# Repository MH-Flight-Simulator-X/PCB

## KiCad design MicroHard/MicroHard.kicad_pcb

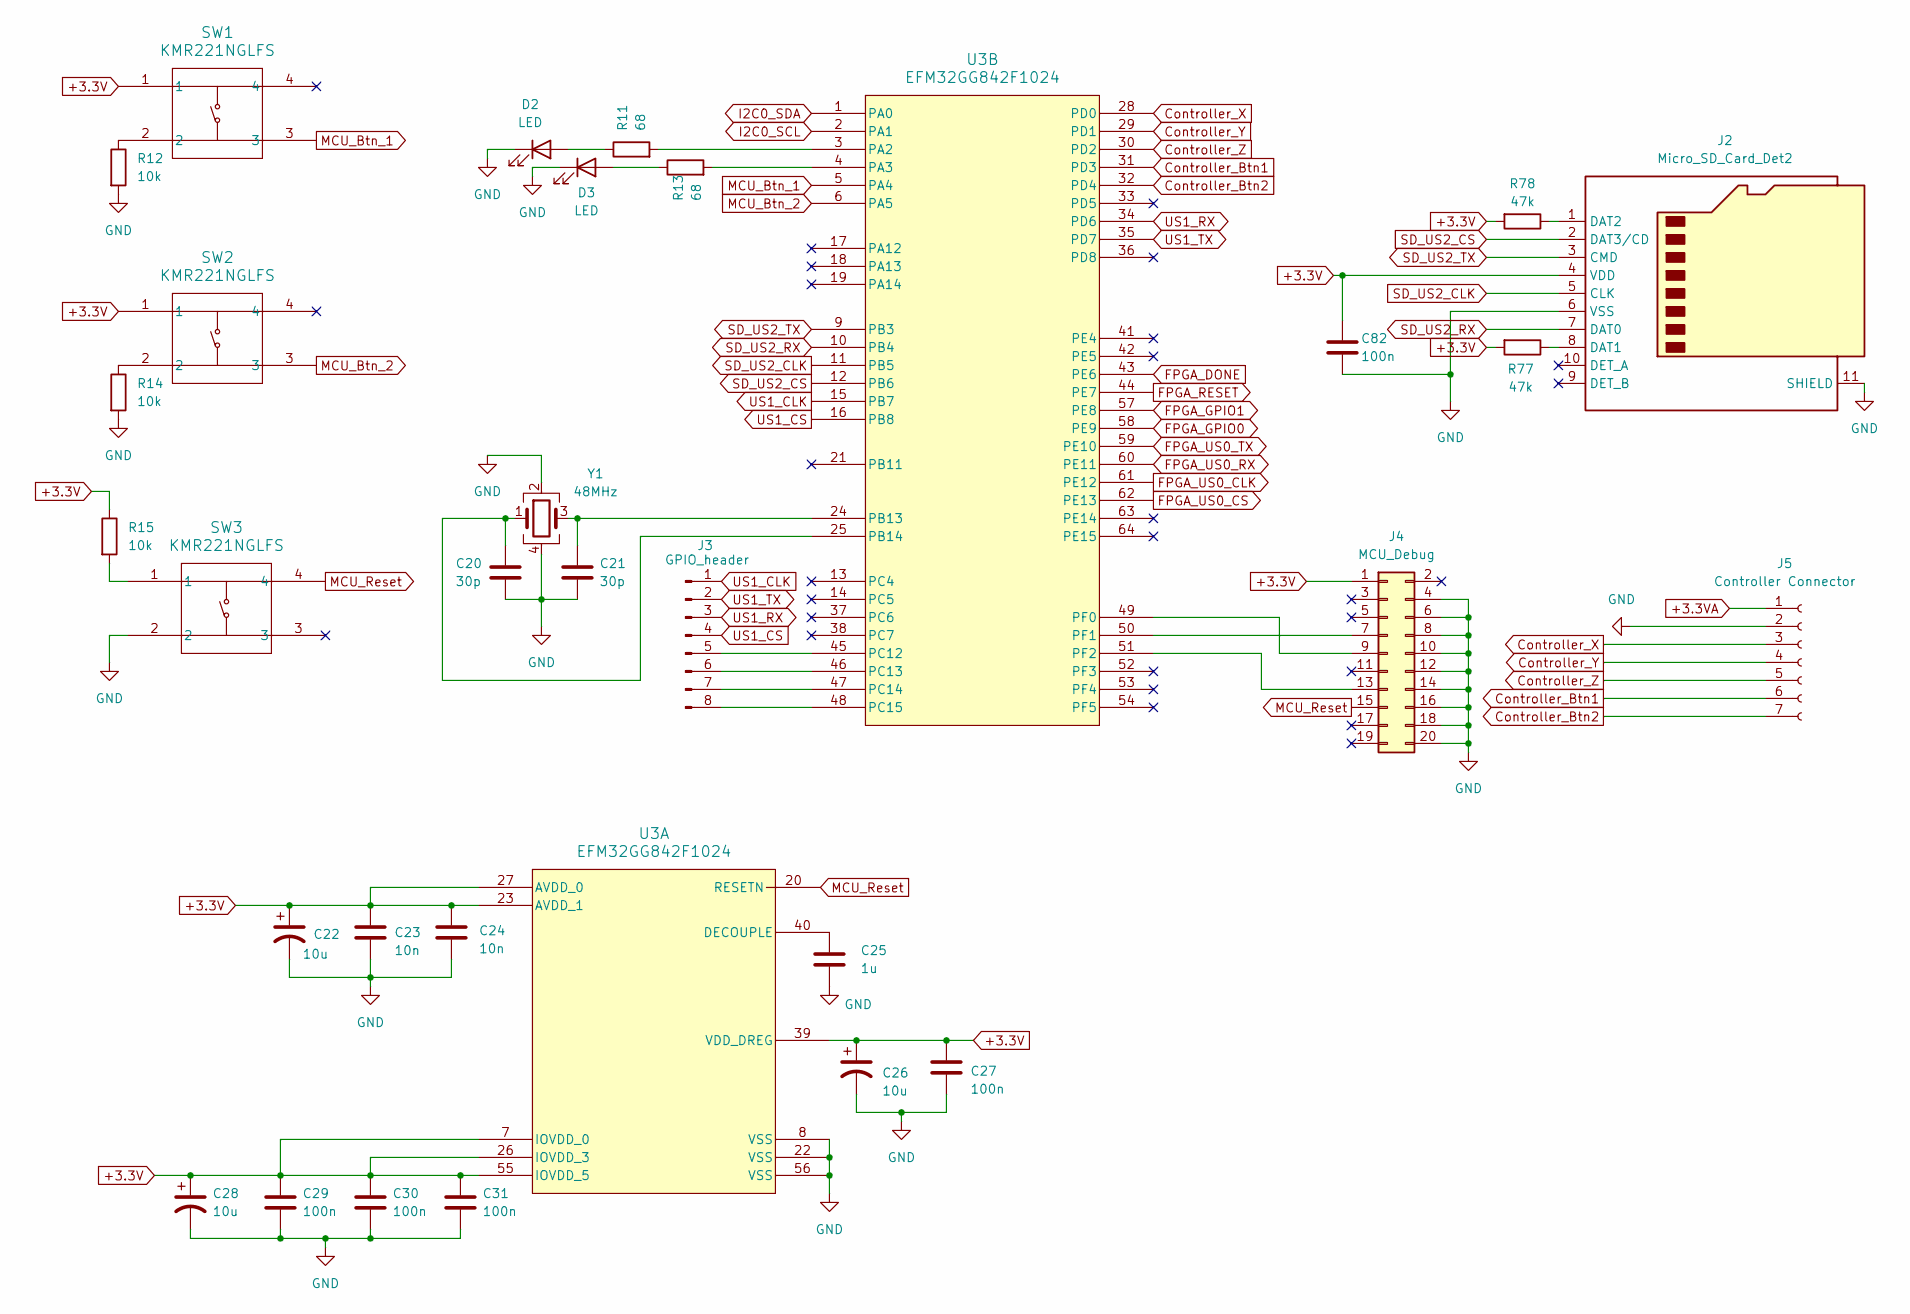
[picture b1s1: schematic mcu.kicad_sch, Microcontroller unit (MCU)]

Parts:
C20, C21: 30p; C_0805_2012Metric_Pad1.18x1.45mm_HandSolder
C22, C26, C28: 10u; C_1206_3216Metric_Pad1.33x1.80mm_HandSolder
C23, C24: 10n; C_1206_3216Metric_Pad1.33x1.80mm_HandSolder
C25: 1u; C_1206_3216Metric_Pad1.33x1.80mm_HandSolder
C27, C29, C30, C31, C82: 100n; C_1206_3216Metric_Pad1.33x1.80mm_HandSolder
D2, D3: LED; LED_1206_3216Metric_Pad1.42x1.75mm_HandSolder
J2: Micro_SD_Card_Det2; microSD_HC_Hirose_DM3AT-SF-PEJM5
J3: GPIO_header; PinHeader_1x08_P2.54mm_Vertical
J4: MCU_Debug; IDC-Header_2x10_P2.54mm_Vertical
J5: Controller Connector; PinHeader_1x07_P2.54mm_Vertical
R11, R13: 68; R_1206_3216Metric_Pad1.30x1.75mm_HandSolder
R12, R14, R15: 10k; R_1206_3216Metric_Pad1.30x1.75mm_HandSolder
R77, R78: 47k; R_1206_3216Metric_Pad1.30x1.75mm_HandSolder
SW1, SW2, SW3: KMR221NGLFS; KMR221_CNK
U3: EFM32GG842F1024; QFP64_10X10
Y1: 48MHz; Crystal_SMD_3225-4Pin_3.2x2.5mm_HandSoldering

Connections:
+3.3V: C22.1, C23.1, C24.1, C26.1, C27.1, C28.1, C29.1, C30.1, C31.1, C82.1, J2.4 (VDD), J4.1, R15.1, R77.2, R78.2, SW1.1, SW2.1, U3.7 (IOVDD_0), U3.23 (AVDD_1), U3.26 (IOVDD_3), U3.27 (AVDD_0), U3.39 (VDD_DREG), U3.55 (IOVDD_5); also elsewhere on the board
+3.3VA: J5.1; also elsewhere on the board
Controller_Btn1: J5.6, U3.31 (PD3)
Controller_Btn2: J5.7, U3.32 (PD4)
Controller_X: J5.3, U3.28 (PD0)
Controller_Y: J5.4, U3.29 (PD1)
Controller_Z: J5.5, U3.30 (PD2)
FPGA_DONE: U3.43 (PE6); also elsewhere on the board
FPGA_GPIO0: U3.58 (PE9); also elsewhere on the board
FPGA_GPIO1: U3.57 (PE8); also elsewhere on the board
FPGA_RESET: U3.44 (PE7); also elsewhere on the board
FPGA_US0_CLK: U3.61 (PE12); also elsewhere on the board
FPGA_US0_CS: U3.62 (PE13); also elsewhere on the board
FPGA_US0_RX: U3.60 (PE11); also elsewhere on the board
FPGA_US0_TX: U3.59 (PE10); also elsewhere on the board
GND: C20.2, C21.2, C22.2, C23.2, C24.2, C25.2, C26.2, C27.2, C28.2, C29.2, C30.2, C31.2, C82.2, D2.1 (K), D3.1 (K), J2.6 (VSS), J2.11 (SHIELD), J4.4, J4.6, J4.8, J4.10, J4.12, J4.14, J4.16, J4.18, J4.20, J5.2, R12.2, R14.2, SW3.2, U3.8 (VSS), U3.22 (VSS), U3.56 (VSS), Y1.2, Y1.4; also elsewhere on the board
I2C0_SCL: U3.2 (PA1); also elsewhere on the board
I2C0_SDA: U3.1 (PA0); also elsewhere on the board
MCU_Btn_1: SW1.3, U3.5 (PA4)
MCU_Btn_2: SW2.3, U3.6 (PA5)
MCU_Reset: J4.15, SW3.4, U3.20 (RESETN)
unnamed: D2.2 (A), R11.1
unnamed: D3.2 (A), R13.1
unnamed: J2.8 (DAT1), R77.1
unnamed: J2.1 (DAT2), R78.1
unnamed: J3.5, U3.45 (PC12)
unnamed: J3.6, U3.46 (PC13)
unnamed: J3.7, U3.47 (PC14)
unnamed: J3.8, U3.48 (PC15)
unnamed: J4.7, U3.50 (PF1)
unnamed: J4.9, U3.49 (PF0)
unnamed: J4.13, U3.51 (PF2)
unnamed: R12.1, SW1.2
unnamed: R14.1, SW2.2
unnamed: R15.2, SW3.1
unnamed: C25.1, U3.40 (DECOUPLE)
unnamed: R11.2, U3.3 (PA2)
unnamed: R13.2, U3.4 (PA3)
unnamed: C21.1, U3.24 (PB13), Y1.3
unnamed: C20.1, U3.25 (PB14), Y1.1
SD_US2_CLK: J2.5 (CLK), U3.11 (PB5)
SD_US2_CS: J2.2 (DAT3/CD), U3.12 (PB6)
SD_US2_RX: J2.7 (DAT0), U3.10 (PB4)
SD_US2_TX: J2.3 (CMD), U3.9 (PB3)
US1_CLK: J3.1, U3.15 (PB7)
US1_CS: J3.4, U3.16 (PB8)
US1_RX: J3.3, U3.34 (PD6)
US1_TX: J3.2, U3.35 (PD7)

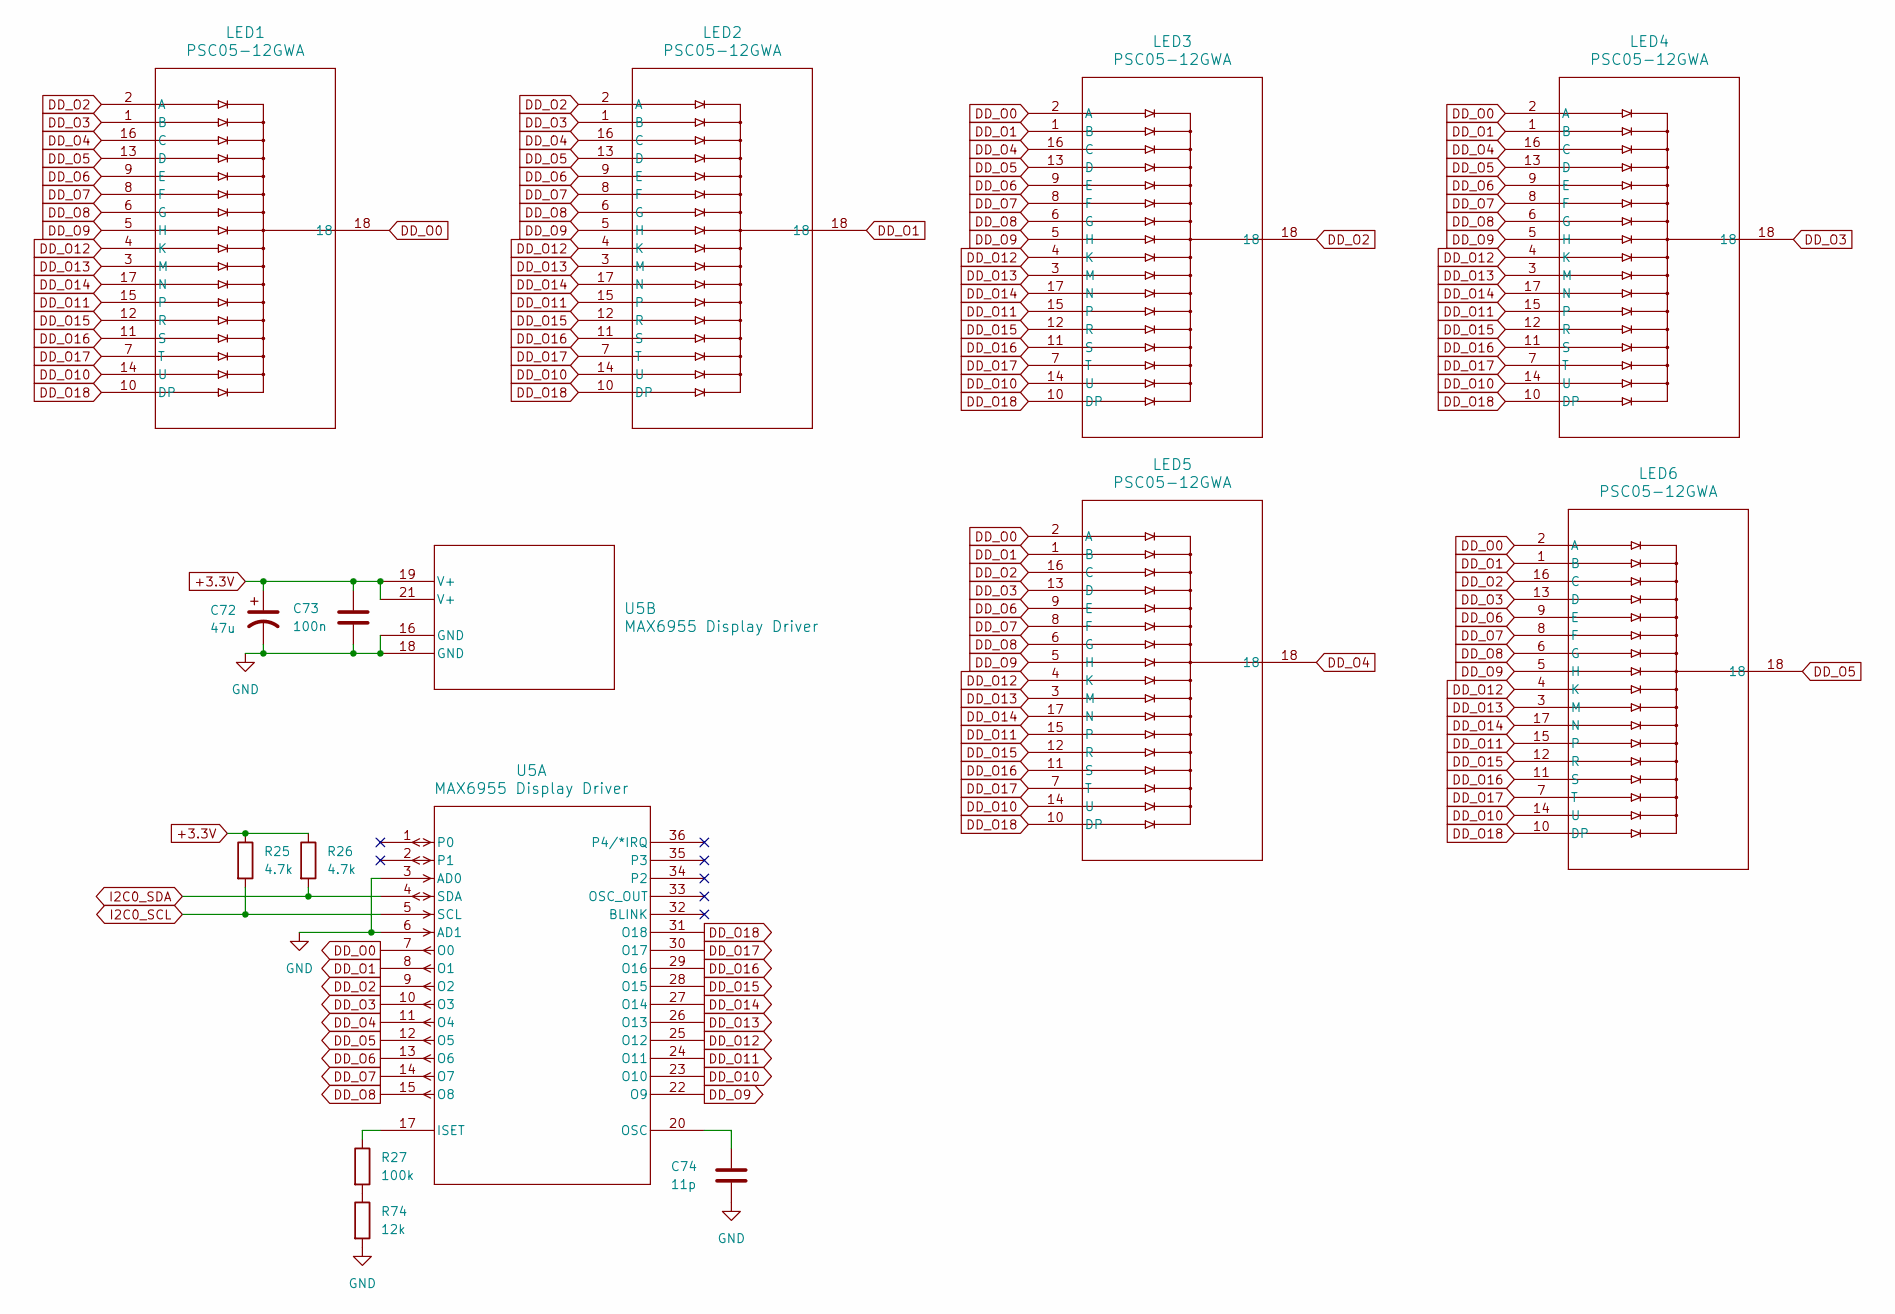
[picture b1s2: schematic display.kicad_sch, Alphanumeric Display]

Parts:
C72: 47u; C_1210_3225Metric_Pad1.33x2.70mm_HandSolder
C73: 100n; C_1206_3216Metric_Pad1.33x1.80mm_HandSolder
C74: 11p; C_0805_2012Metric_Pad1.18x1.45mm_HandSolder
LED1, LED2, LED3, LED4, LED5, LED6: PSC05-12GWA; PSC05-12GWA_LTO
R25, R26: 4.7k; R_1206_3216Metric_Pad1.30x1.75mm_HandSolder
R27: 100k; R_1206_3216Metric_Pad1.30x1.75mm_HandSolder
R74: 12k; R_1206_3216Metric_Pad1.30x1.75mm_HandSolder
U5: MAX6955 Display Driver; 21-0040_A36&plus_2_MXM

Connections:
+3.3V: C72.1, C73.1, R25.1, R26.1, U5.19 (V+), U5.21 (V+); also elsewhere on the board
DD_O0: LED1.18, LED3.2 (A), LED4.2 (A), LED5.2 (A), LED6.2 (A), U5.7 (O0)
DD_O1: LED2.18, LED3.1 (B), LED4.1 (B), LED5.1 (B), LED6.1 (B), U5.8 (O1)
DD_O2: LED1.2 (A), LED2.2 (A), LED3.18, LED5.16 (C), LED6.16 (C), U5.9 (O2)
DD_O3: LED1.1 (B), LED2.1 (B), LED4.18, LED5.13 (D), LED6.13 (D), U5.10 (O3)
DD_O4: LED1.16 (C), LED2.16 (C), LED3.16 (C), LED4.16 (C), LED5.18, U5.11 (O4)
DD_O5: LED1.13 (D), LED2.13 (D), LED3.13 (D), LED4.13 (D), LED6.18, U5.12 (O5)
DD_O6: LED1.9 (E), LED2.9 (E), LED3.9 (E), LED4.9 (E), LED5.9 (E), LED6.9 (E), U5.13 (O6)
DD_O7: LED1.8 (F), LED2.8 (F), LED3.8 (F), LED4.8 (F), LED5.8 (F), LED6.8 (F), U5.14 (O7)
DD_O8: LED1.6 (G), LED2.6 (G), LED3.6 (G), LED4.6 (G), LED5.6 (G), LED6.6 (G), U5.15 (O8)
DD_O9: LED1.5 (H), LED2.5 (H), LED3.5 (H), LED4.5 (H), LED5.5 (H), LED6.5 (H), U5.22 (O9)
DD_O10: LED1.14 (U), LED2.14 (U), LED3.14 (U), LED4.14 (U), LED5.14 (U), LED6.14 (U), U5.23 (O10)
DD_O11: LED1.15, LED2.15, LED3.15, LED4.15, LED5.15, LED6.15, U5.24 (O11)
DD_O12: LED1.4 (K), LED2.4 (K), LED3.4 (K), LED4.4 (K), LED5.4 (K), LED6.4 (K), U5.25 (O12)
DD_O13: LED1.3 (M), LED2.3 (M), LED3.3 (M), LED4.3 (M), LED5.3 (M), LED6.3 (M), U5.26 (O13)
DD_O14: LED1.17 (N), LED2.17 (N), LED3.17 (N), LED4.17 (N), LED5.17 (N), LED6.17 (N), U5.27 (O14)
DD_O15: LED1.12 (R), LED2.12 (R), LED3.12 (R), LED4.12 (R), LED5.12 (R), LED6.12 (R), U5.28 (O15)
DD_O16: LED1.11 (S), LED2.11 (S), LED3.11 (S), LED4.11 (S), LED5.11 (S), LED6.11 (S), U5.29 (O16)
DD_O17: LED1.7 (T), LED2.7 (T), LED3.7 (T), LED4.7 (T), LED5.7 (T), LED6.7 (T), U5.30 (O17)
DD_O18: LED1.10 (DP), LED2.10 (DP), LED3.10 (DP), LED4.10 (DP), LED5.10 (DP), LED6.10 (DP), U5.31 (O18)
GND: C72.2, C73.2, C74.2, R74.2, U5.3 (AD0), U5.6 (AD1), U5.16 (GND), U5.18 (GND); also elsewhere on the board
I2C0_SCL: R25.2, U5.5 (SCL); also elsewhere on the board
I2C0_SDA: R26.2, U5.4 (SDA); also elsewhere on the board
unnamed: R27.2, R74.1
unnamed: R27.1, U5.17 (ISET)
unnamed: C74.1, U5.20 (OSC)

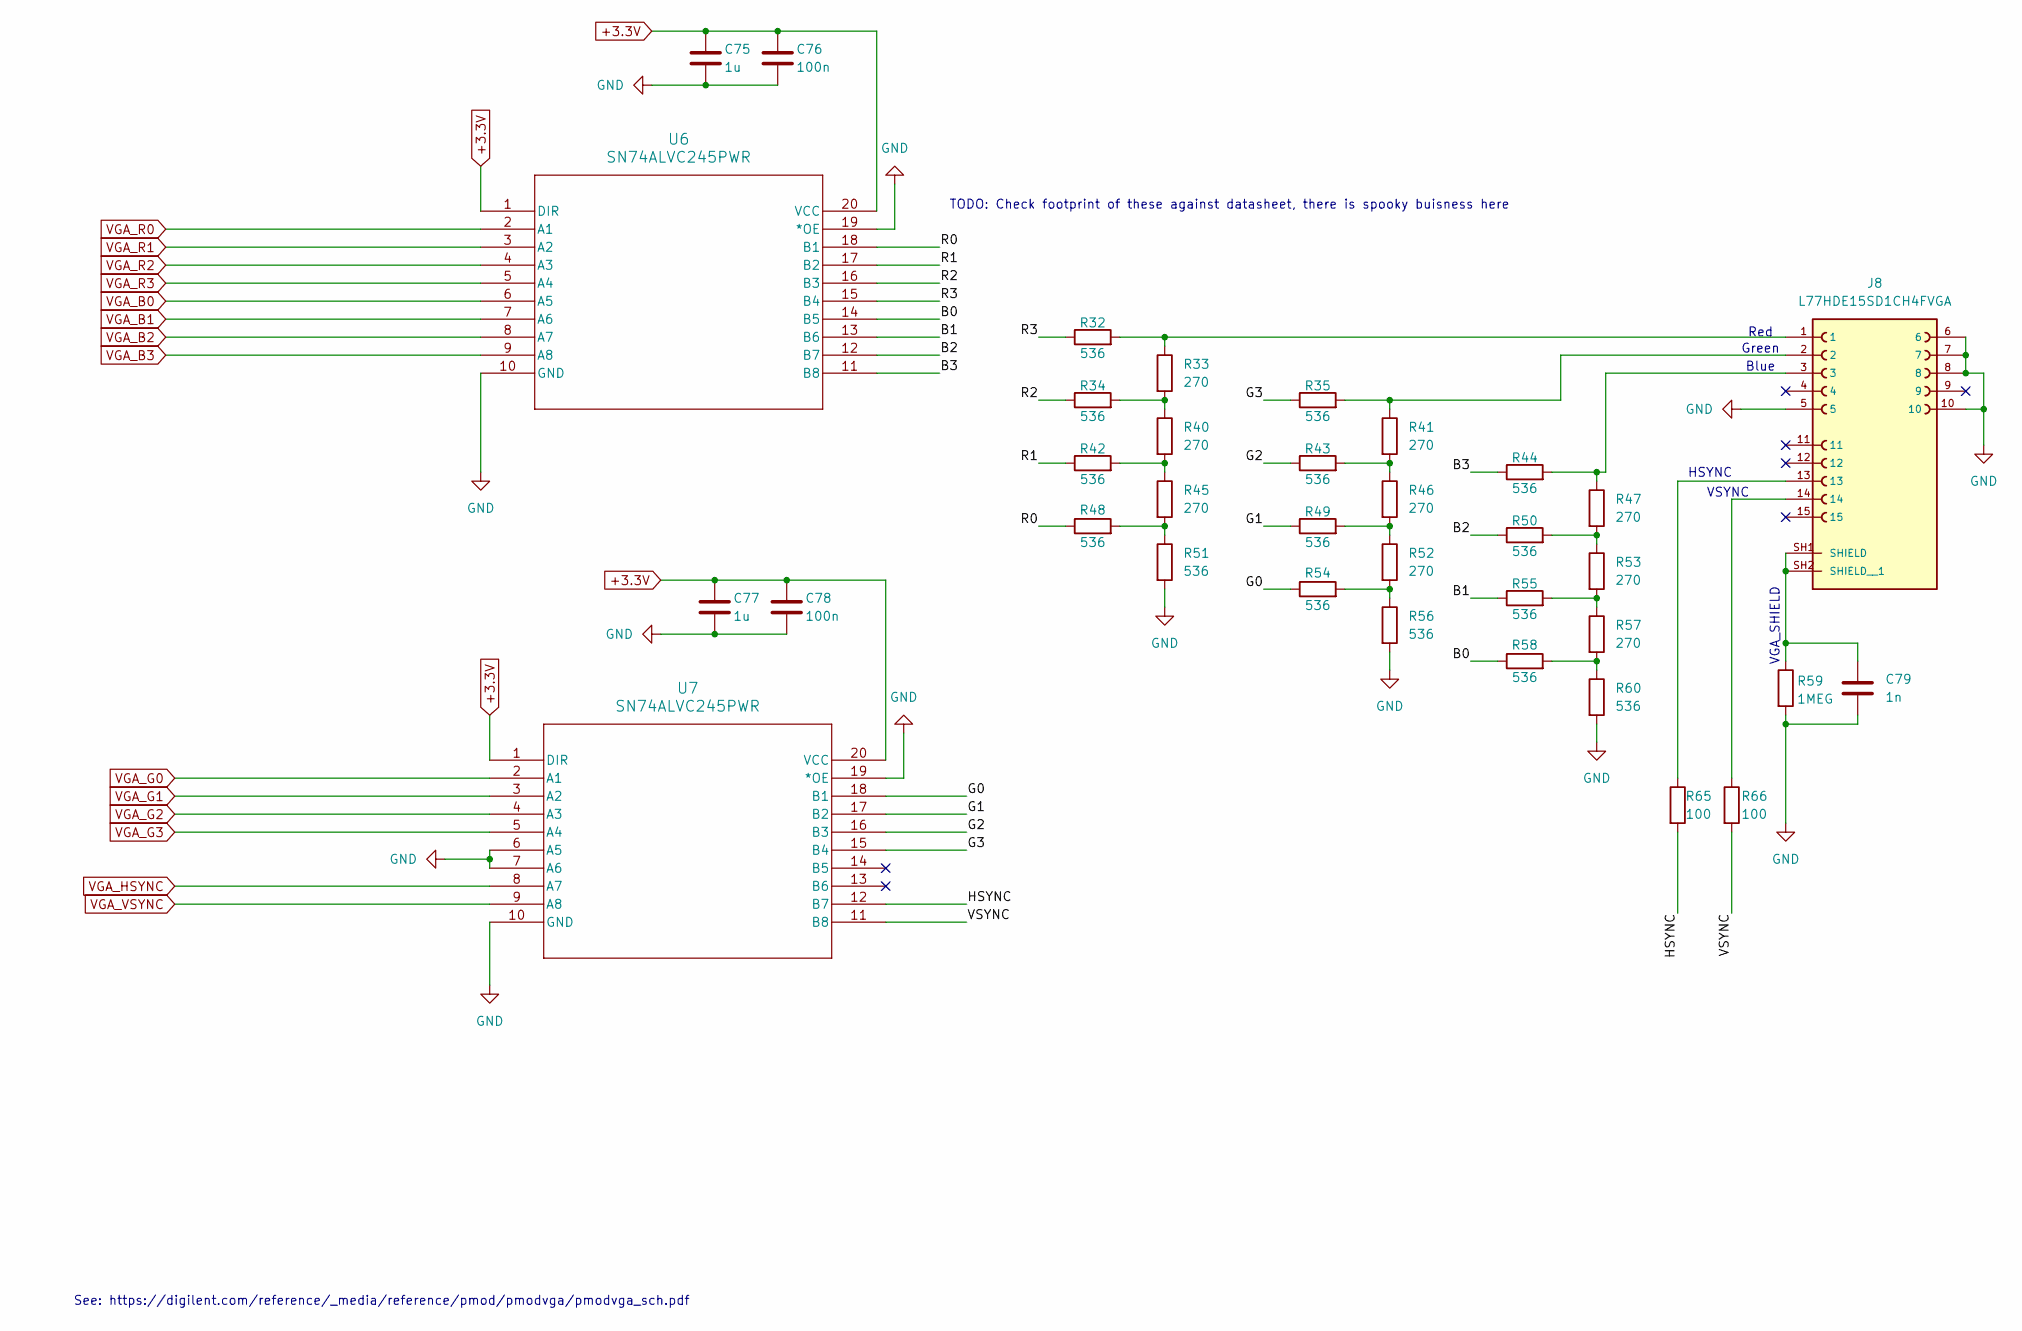
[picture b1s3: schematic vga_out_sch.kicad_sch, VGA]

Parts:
C75, C77: 1u; C_1206_3216Metric_Pad1.33x1.80mm_HandSolder
C76, C78: 100n; C_1206_3216Metric_Pad1.33x1.80mm_HandSolder
C79: 1n; C_0805_2012Metric_Pad1.18x1.45mm_HandSolder
J8: L77HDE15SD1CH4FVGA; AMPHENOL_L77HDE15SD1CH4FVGA; PARTREV 1
R32, R34, R35, R42, R43, R44, R48, R49, R50, R51, R54, R55, R56, R58, R60: 536; R_1206_3216Metric_Pad1.30x1.75mm_HandSolder
R33, R40, R41, R45, R46, R47, R52, R53, R57: 270; R_1206_3216Metric_Pad1.30x1.75mm_HandSolder
R59: 1MEG; R_1206_3216Metric_Pad1.30x1.75mm_HandSolder
R65, R66: 100; R_1206_3216Metric_Pad1.30x1.75mm_HandSolder
U6, U7: SN74ALVC245PWR; PW20

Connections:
+3.3V: C75.1, C76.1, C77.1, C78.1, U6.1 (DIR), U6.20 (VCC), U7.1 (DIR), U7.20 (VCC); also elsewhere on the board
/VGA out/B0: R58.1, U6.14 (B5)
/VGA out/B1: R55.1, U6.13 (B6)
/VGA out/B2: R50.1, U6.12 (B7)
/VGA out/B3: R44.1, U6.11 (B8)
/VGA out/G0: R54.1, U7.18 (B1)
/VGA out/G1: R49.1, U7.17 (B2)
/VGA out/G2: R43.1, U7.16 (B3)
/VGA out/G3: R35.1, U7.15 (B4)
/VGA out/HSYNC: R65.2, U7.12 (B7)
/VGA out/R0: R48.1, U6.18 (B1)
/VGA out/R1: R42.1, U6.17 (B2)
/VGA out/R2: R34.1, U6.16 (B3)
/VGA out/R3: R32.1, U6.15 (B4)
/VGA out/VSYNC: R66.2, U7.11 (B8)
GND: C75.2, C76.2, C77.2, C78.2, C79.2, J8.5, J8.6, J8.7, J8.8, J8.10, R51.2, R56.2, R59.2, R60.2, U6.10 (GND), U6.19 (*OE), U7.6 (A5), U7.7 (A6), U7.10 (GND), U7.19 (*OE); also elsewhere on the board
unnamed: J8.1, R32.2, R33.1
unnamed: J8.2, R35.2, R41.1
unnamed: J8.3, R44.2, R47.1
unnamed: J8.13, R65.1
unnamed: J8.14, R66.1
unnamed: C79.1, J8.SH1 (SHIELD), J8.SH2 (SHIELD__1), R59.1
unnamed: R33.2, R34.2, R40.1
unnamed: R40.2, R42.2, R45.1
unnamed: R41.2, R43.2, R46.1
unnamed: R45.2, R48.2, R51.1
unnamed: R46.2, R49.2, R52.1
unnamed: R47.2, R50.2, R53.1
unnamed: R52.2, R54.2, R56.1
unnamed: R53.2, R55.2, R57.1
unnamed: R57.2, R58.2, R60.1
VGA_B0: U6.6 (A5); also elsewhere on the board
VGA_B1: U6.7 (A6); also elsewhere on the board
VGA_B2: U6.8 (A7); also elsewhere on the board
VGA_B3: U6.9 (A8); also elsewhere on the board
VGA_G0: U7.2 (A1); also elsewhere on the board
VGA_G1: U7.3 (A2); also elsewhere on the board
VGA_G2: U7.4 (A3); also elsewhere on the board
VGA_G3: U7.5 (A4); also elsewhere on the board
VGA_HSYNC: U7.8 (A7); also elsewhere on the board
VGA_R0: U6.2 (A1); also elsewhere on the board
VGA_R1: U6.3 (A2); also elsewhere on the board
VGA_R2: U6.4 (A3); also elsewhere on the board
VGA_R3: U6.5 (A4); also elsewhere on the board
VGA_VSYNC: U7.9 (A8); also elsewhere on the board

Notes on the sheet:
HSYNC
Blue
VGA_SHIELD
Green
See: https://digilent.com/reference/_media/reference/pmod/pmodvga/pmodvga_sch.pdf
TODO: Check footprint of these against datasheet, there is spooky buisness here
Red
VSYNC

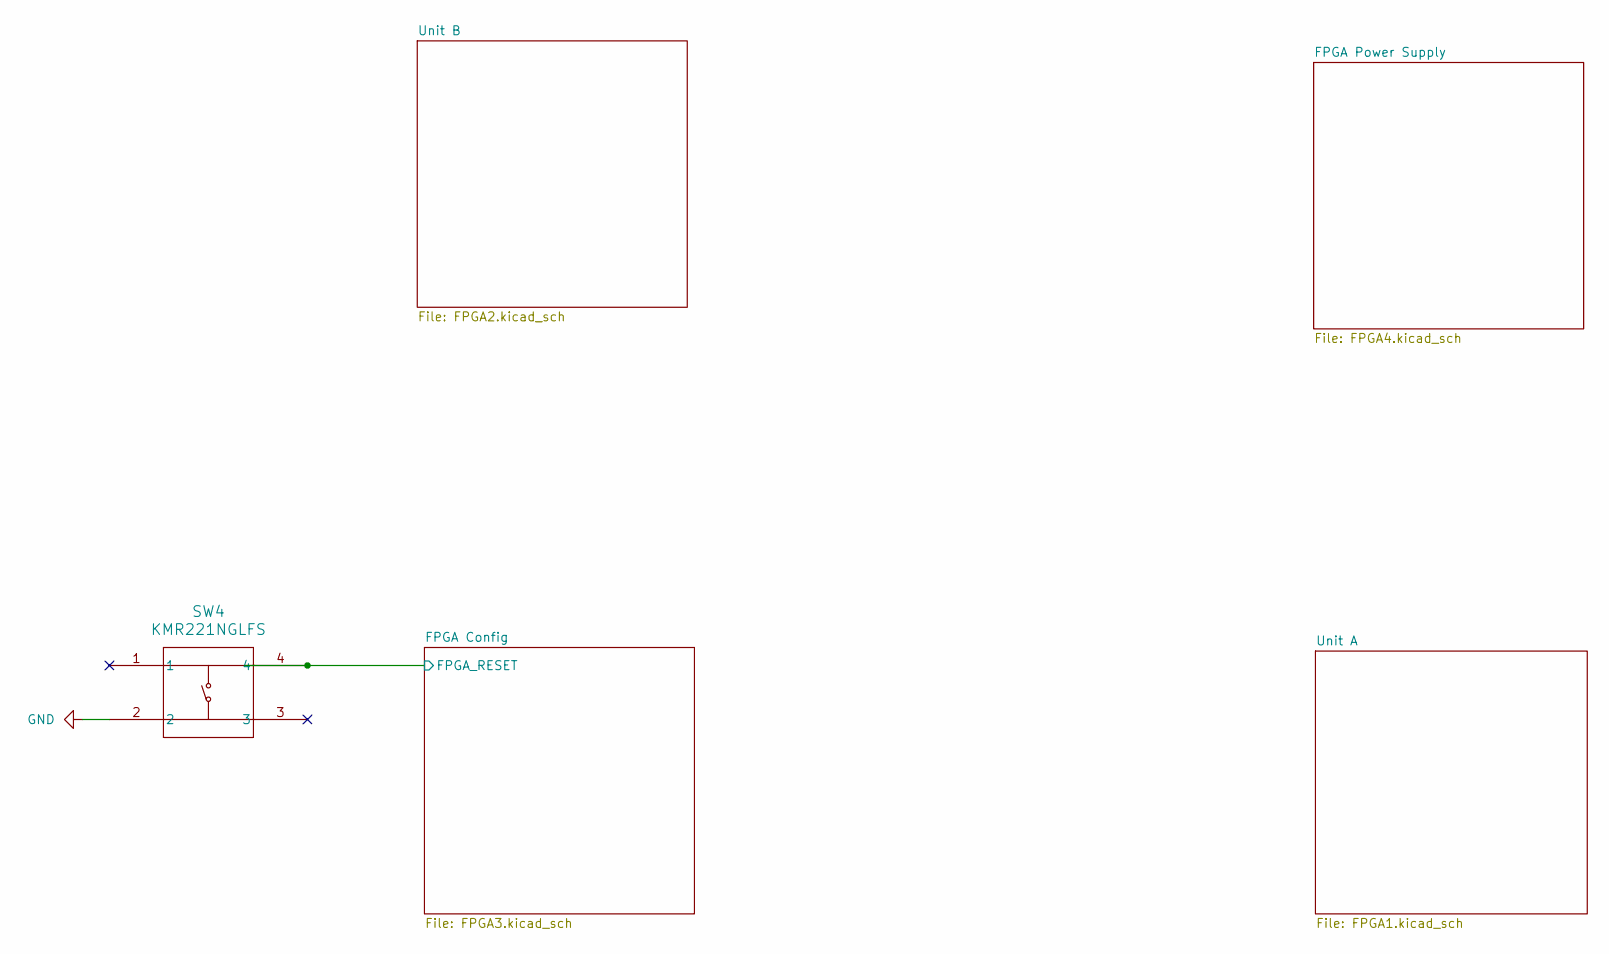
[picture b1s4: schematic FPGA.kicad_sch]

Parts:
SW4: KMR221NGLFS; KMR221_CNK

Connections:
FPGA_RESET: SW4.4; also elsewhere on the board
GND: SW4.2; also elsewhere on the board

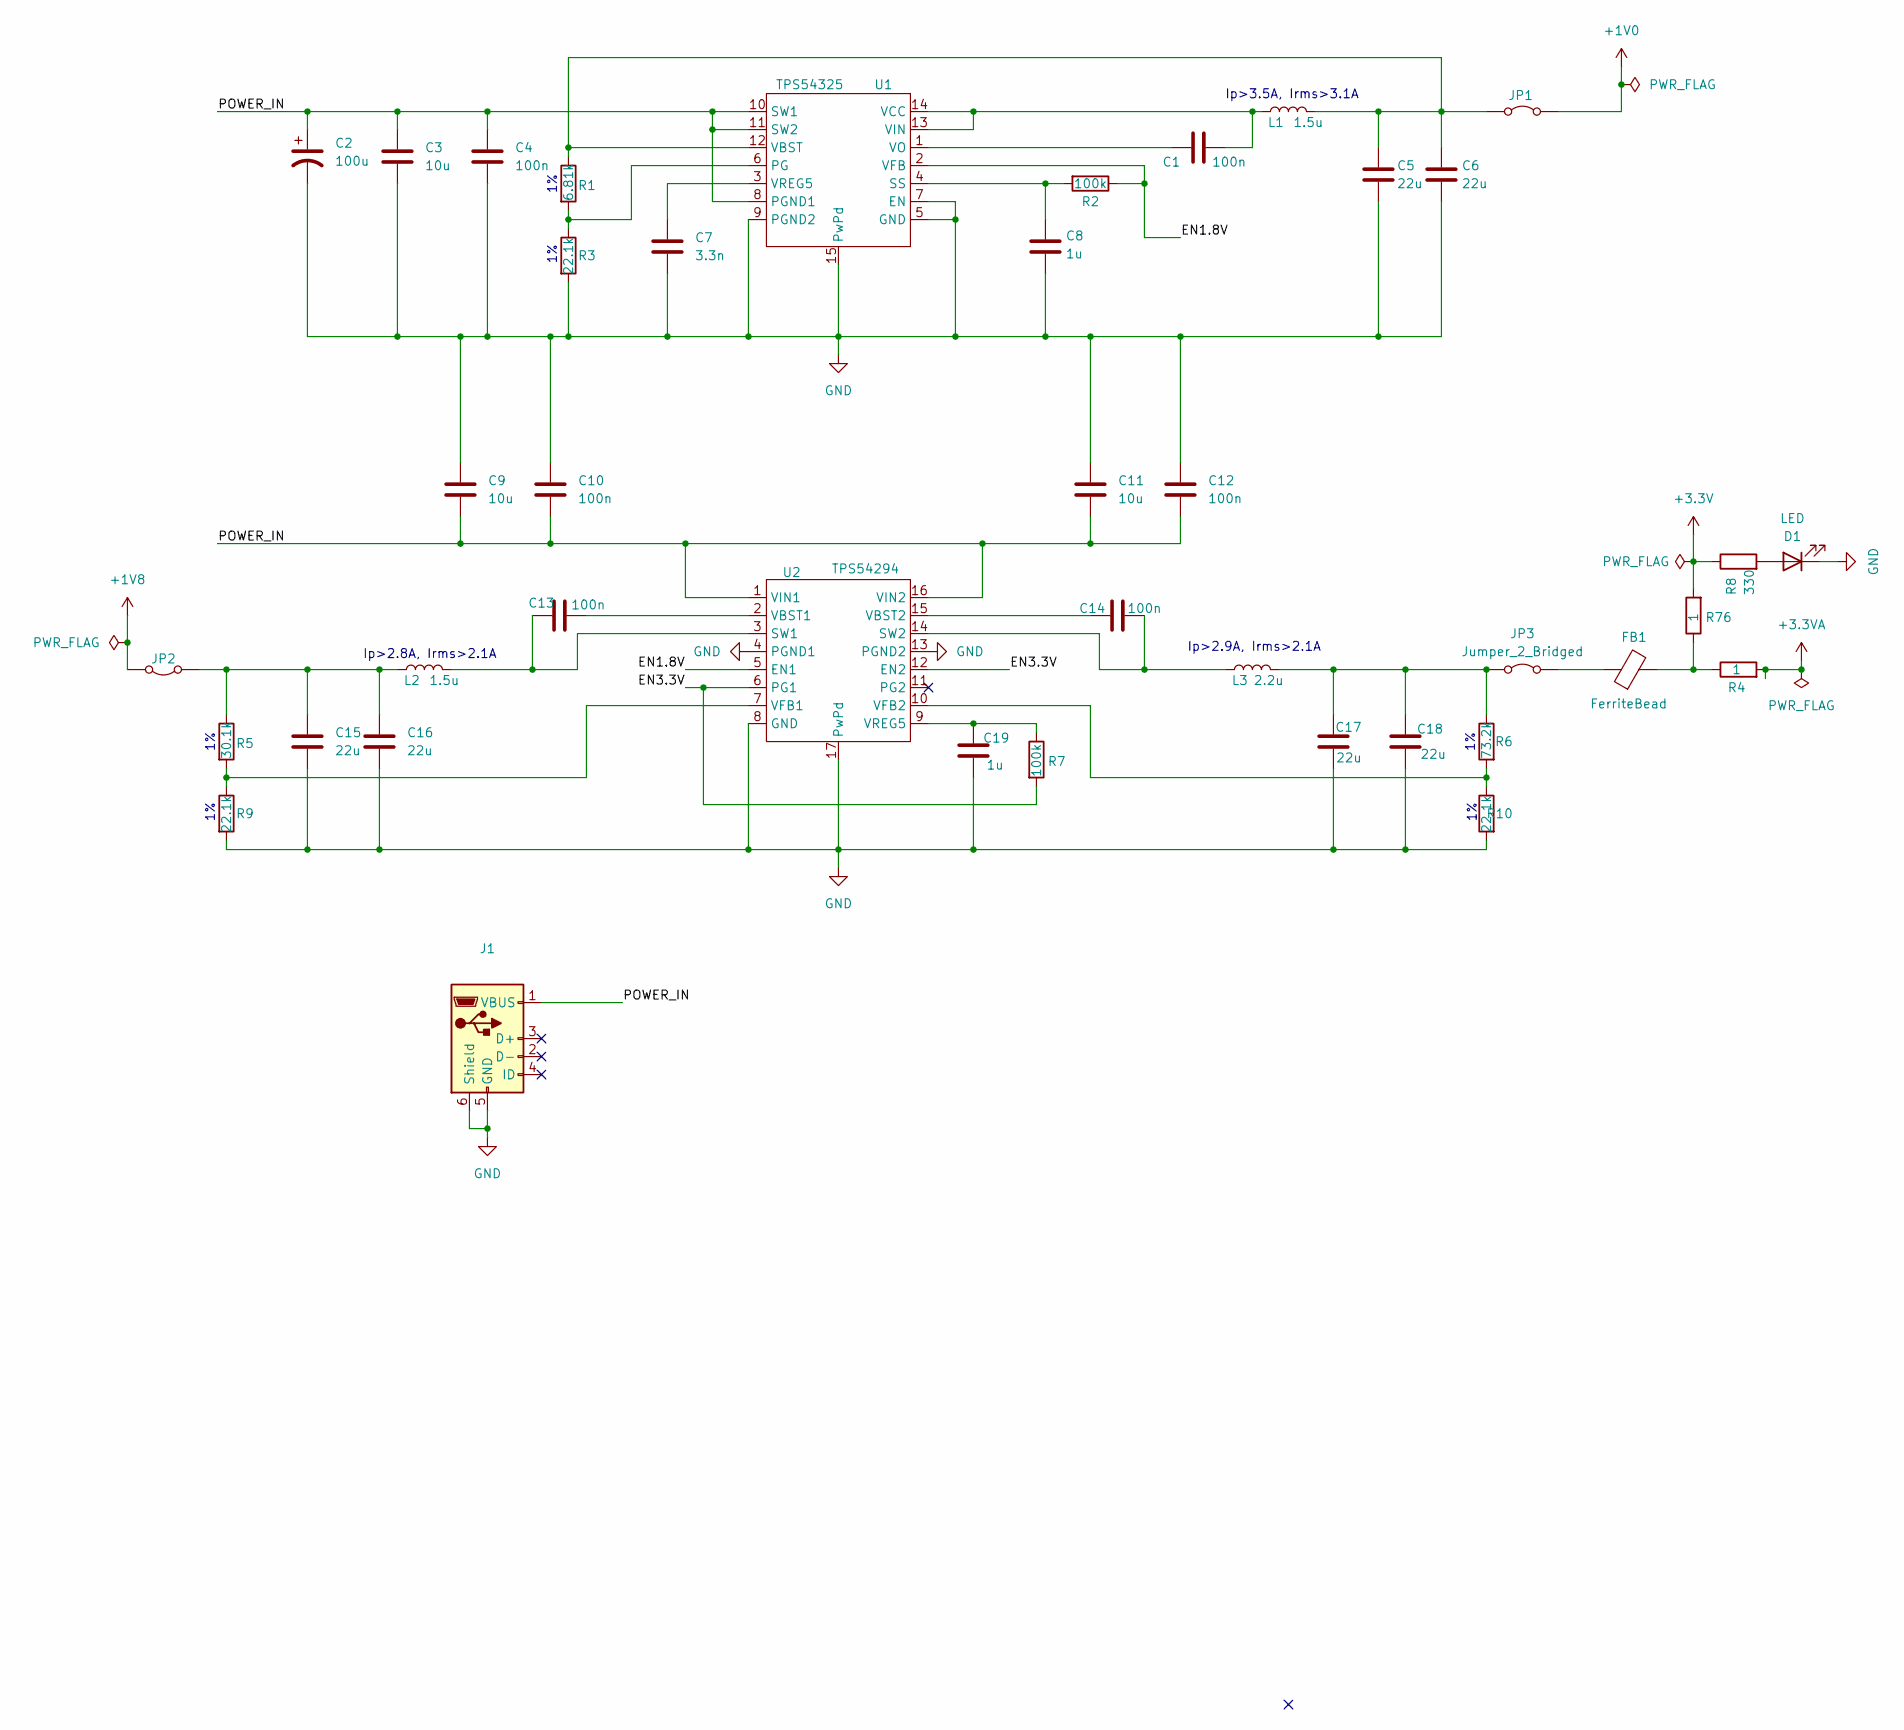
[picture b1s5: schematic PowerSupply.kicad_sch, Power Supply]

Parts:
C1, C4, C10, C12, C13, C14: 100n; C_1206_3216Metric_Pad1.33x1.80mm_HandSolder
C2: 100u; C_1210_3225Metric_Pad1.33x2.70mm_HandSolder
C3, C9, C11: 10u; C_1206_3216Metric_Pad1.33x1.80mm_HandSolder
C5, C6, C15, C16, C17, C18: 22u; C_1206_3216Metric_Pad1.33x1.80mm_HandSolder
C7: 3.3n; C_1206_3216Metric_Pad1.33x1.80mm_HandSolder
C8, C19: 1u; C_1206_3216Metric_Pad1.33x1.80mm_HandSolder
D1: LED; LED_1206_3216Metric_Pad1.42x1.75mm_HandSolder
FB1: FerriteBead; R_1206_3216Metric_Pad1.30x1.75mm_HandSolder
J1: USB_B_Micro; USB_Micro-B_Amphenol_10118194_Horizontal
JP1, JP2, JP3: Jumper_2_Bridged; PinHeader_1x02_P2.54mm_Vertical
L1, L2: 1.5u; IND_8357022_WRE
L3: 2.2u; IND_8357022_WRE
R1: 6.81k; R_1206_3216Metric_Pad1.30x1.75mm_HandSolder
R2, R7: 100k; R_1206_3216Metric_Pad1.30x1.75mm_HandSolder
R3, R9, R10: 22.1k; R_1206_3216Metric_Pad1.30x1.75mm_HandSolder
R4, R76: 1; R_1206_3216Metric_Pad1.30x1.75mm_HandSolder
R5: 30.1k; R_1206_3216Metric_Pad1.30x1.75mm_HandSolder
R6: 73.2k; R_1206_3216Metric_Pad1.30x1.75mm_HandSolder
R8: 330; R_1206_3216Metric_Pad1.30x1.75mm_HandSolder
U1: TPS54325; PWP14_2P31X2P46
U2: TPS54294; PWP16_2P31X2P46

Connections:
+1V0: JP1.2 (B); also elsewhere on the board
+1V8: JP2.2 (B); also elsewhere on the board
+3.3V: R8.1, R76.2; also elsewhere on the board
+3.3VA: R4.2; also elsewhere on the board
/Power Supply/EN1.8V: R2.1, U1.2 (VFB), U2.5 (EN1)
/Power Supply/EN3.3V: R7.2, U2.6 (PG1), U2.12 (EN2)
/Power Supply/POWER_IN: C2.1, C3.1, C4.1, C9.2, C10.2, C11.2, C12.2, J1.1 (VBUS), U1.8 (PGND1), U1.10 (SW1), U1.11 (SW2), U2.1 (VIN1), U2.16 (VIN2)
GND: C2.2, C3.2, C4.2, C5.2, C6.2, C7.2, C8.2, C9.1, C10.1, C11.1, C12.1, C15.2, C16.2, C17.2, C18.2, C19.2, D1.1 (K), J1.5 (GND), J1.6 (Shield), R3.2, R9.2, R10.2, U1.5 (GND), U1.7 (EN), U1.9 (PGND2), U1.15 (PwPd), U2.4 (PGND1), U2.8 (GND), U2.13 (PGND2), U2.17 (PwPd), U2.V; also elsewhere on the board
unnamed: D1.2 (A), R8.2
unnamed: FB1.2, R4.1, R76.1
unnamed: C5.1, C6.1, JP1.1 (A), L1.2, R1.1, U1.12 (VBST)
unnamed: C15.1, C16.1, JP2.1 (A), L2.1, R5.1
unnamed: C17.1, C18.1, JP3.1 (A), L3.1, R6.1
unnamed: FB1.1, JP3.2 (B)
unnamed: R1.2, R3.1, U1.6 (PG)
unnamed: C8.1, R2.2, U1.4 (SS)
unnamed: C1.1, L1.1, U1.13 (VIN), U1.14 (VCC)
unnamed: C1.2, U1.1 (VO)
unnamed: C7.1, U1.3 (VREG5)
unnamed: C13.1, L2.2, U2.3 (SW1)
unnamed: C14.1, L3.2, U2.14 (SW2)
unnamed: C13.2, U2.2 (VBST1)
unnamed: C14.2, U2.15 (VBST2)
unnamed: R5.2, R9.1, U2.7 (VFB1)
unnamed: R6.2, R10.1, U2.10 (VFB2)
unnamed: C19.1, R7.1, U2.9 (VREG5)

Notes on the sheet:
Ip>2.9A, Irms>2.1A
Ip>3.5A, Irms>3.1A
Ip>2.8A, Irms>2.1A
